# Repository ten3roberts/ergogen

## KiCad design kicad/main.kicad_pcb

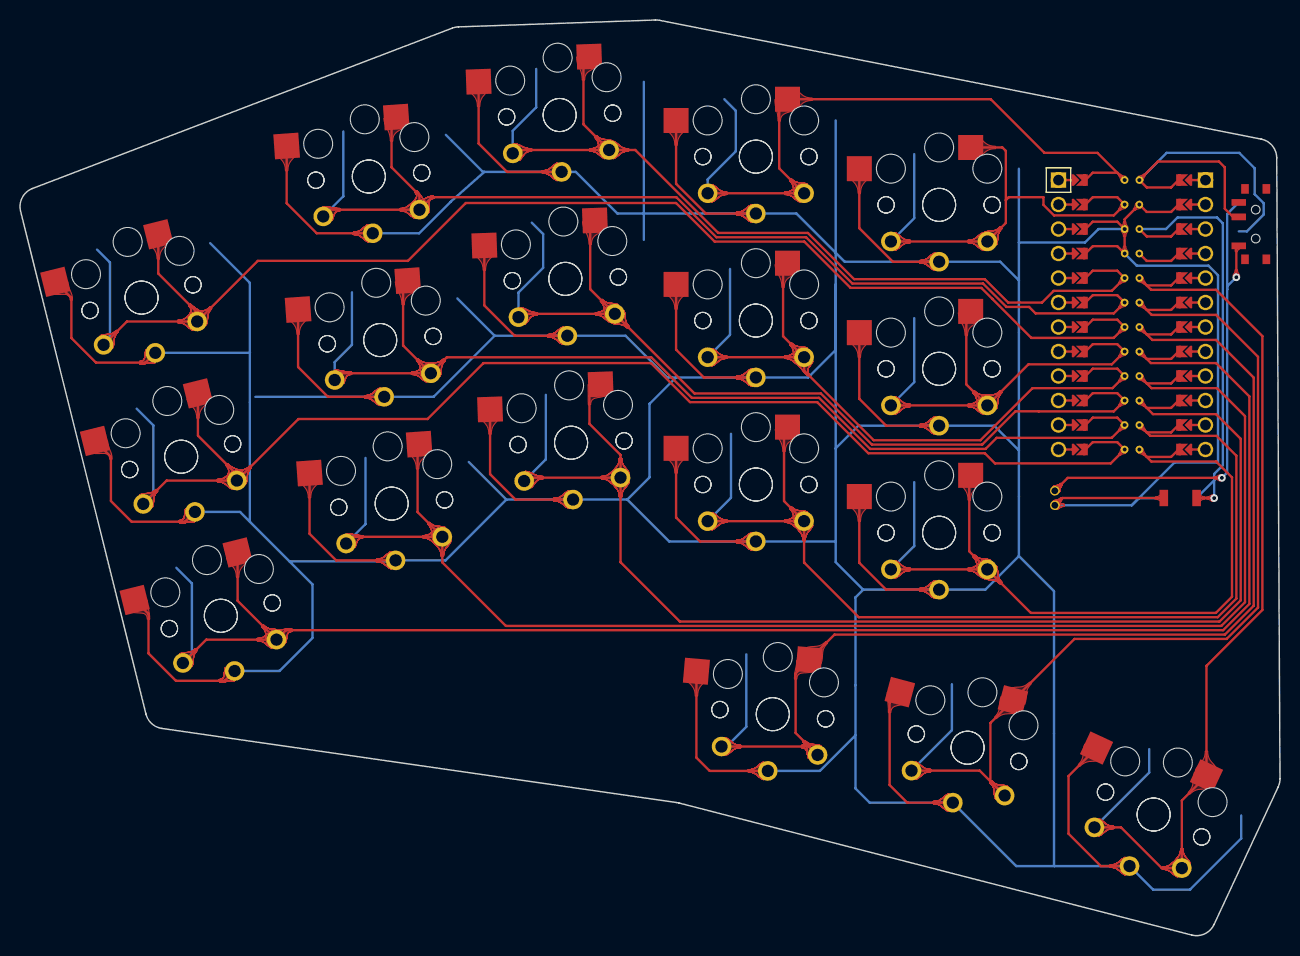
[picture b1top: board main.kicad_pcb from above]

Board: 2 copper layers, 130.7 x 94.9 mm, 37 parts (0 on the bottom side), 19 nets.

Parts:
MCU1: ProMicro
S1, S2, S3, S4, S5, S6, S7, S8, S9, S10, S11, S12, S13, S14, S15, S16, S17, S18, S19, S20, S21, S22, S23, S24, S25, S26, S27, S28, S29, S30, S31, S32, S33, S34, S35, S36: PG1350

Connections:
GND: MCU1.2, MCU1.21, MCU1.22, S1.2, S2.2, S3.2, S4.2, S5.2, S6.2, S7.2, S8.2, S9.2, S10.2, S11.2, S12.2, S13.2, S14.2, S15.2, S16.2, S17.2, S18.2, S19.2, S20.2, S21.2, S22.2, S23.2, S24.2, S25.2, S26.2, S27.2, S28.2, S29.2, S30.2, S31.2, S32.2, S33.2, S34.2, S35.2, S36.2
P0: MCU1.23, S29.1, S30.1
P1: MCU1.24, S23.1, S24.1
P2: MCU1.20, S17.1, S18.1
P3: MCU1.19, S11.1, S12.1
P4: MCU1.18, S5.1, S6.1
P5: MCU1.17, S27.1, S28.1
P6: MCU1.16, S21.1, S22.1
P7: MCU1.15, S15.1, S16.1
P8: MCU1.14, S9.1, S10.1
P9: MCU1.13, S3.1, S4.1
P10: MCU1.12, S25.1, S26.1
P14: MCU1.10, S13.1, S14.1
P15: MCU1.9, S7.1, S8.1
P16: MCU1.11, S19.1, S20.1
P18: MCU1.8, S1.1, S2.1
P19: MCU1.7, S31.1, S32.1
P20: MCU1.6, S33.1, S34.1
P21: MCU1.5, S35.1, S36.1

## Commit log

2022-07-17 feat: extra footprints
2022-07-17 feat: obsidian board
2022-07-17 fix(obsidian): outline
2022-07-19 feat: point nets and switch positioning
2022-07-23 fix: staggering
2022-07-23 fix: rotation and stagger
2022-07-23 feat: per key through holes
2022-07-23 fix: nets
2022-07-24 feat: routing
2022-07-24 wip: routing
2022-07-24 chore: finish routing
2022-07-24 chore: straighten paths
2022-07-24 feat: teardrops
2022-07-24 feat: rounded tracks
2022-07-26 fix: reset button placement
2022-07-26 chore: regenerate teardrops
2022-07-27 fix: smd teardrops
2023-01-11 chore: add final pcb files
